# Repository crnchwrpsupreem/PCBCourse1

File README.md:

# PCBCourse1
Course 1 of 3 PCB design courses through Fedevel: Phils Lab Mixed signal hardware design with Kicad

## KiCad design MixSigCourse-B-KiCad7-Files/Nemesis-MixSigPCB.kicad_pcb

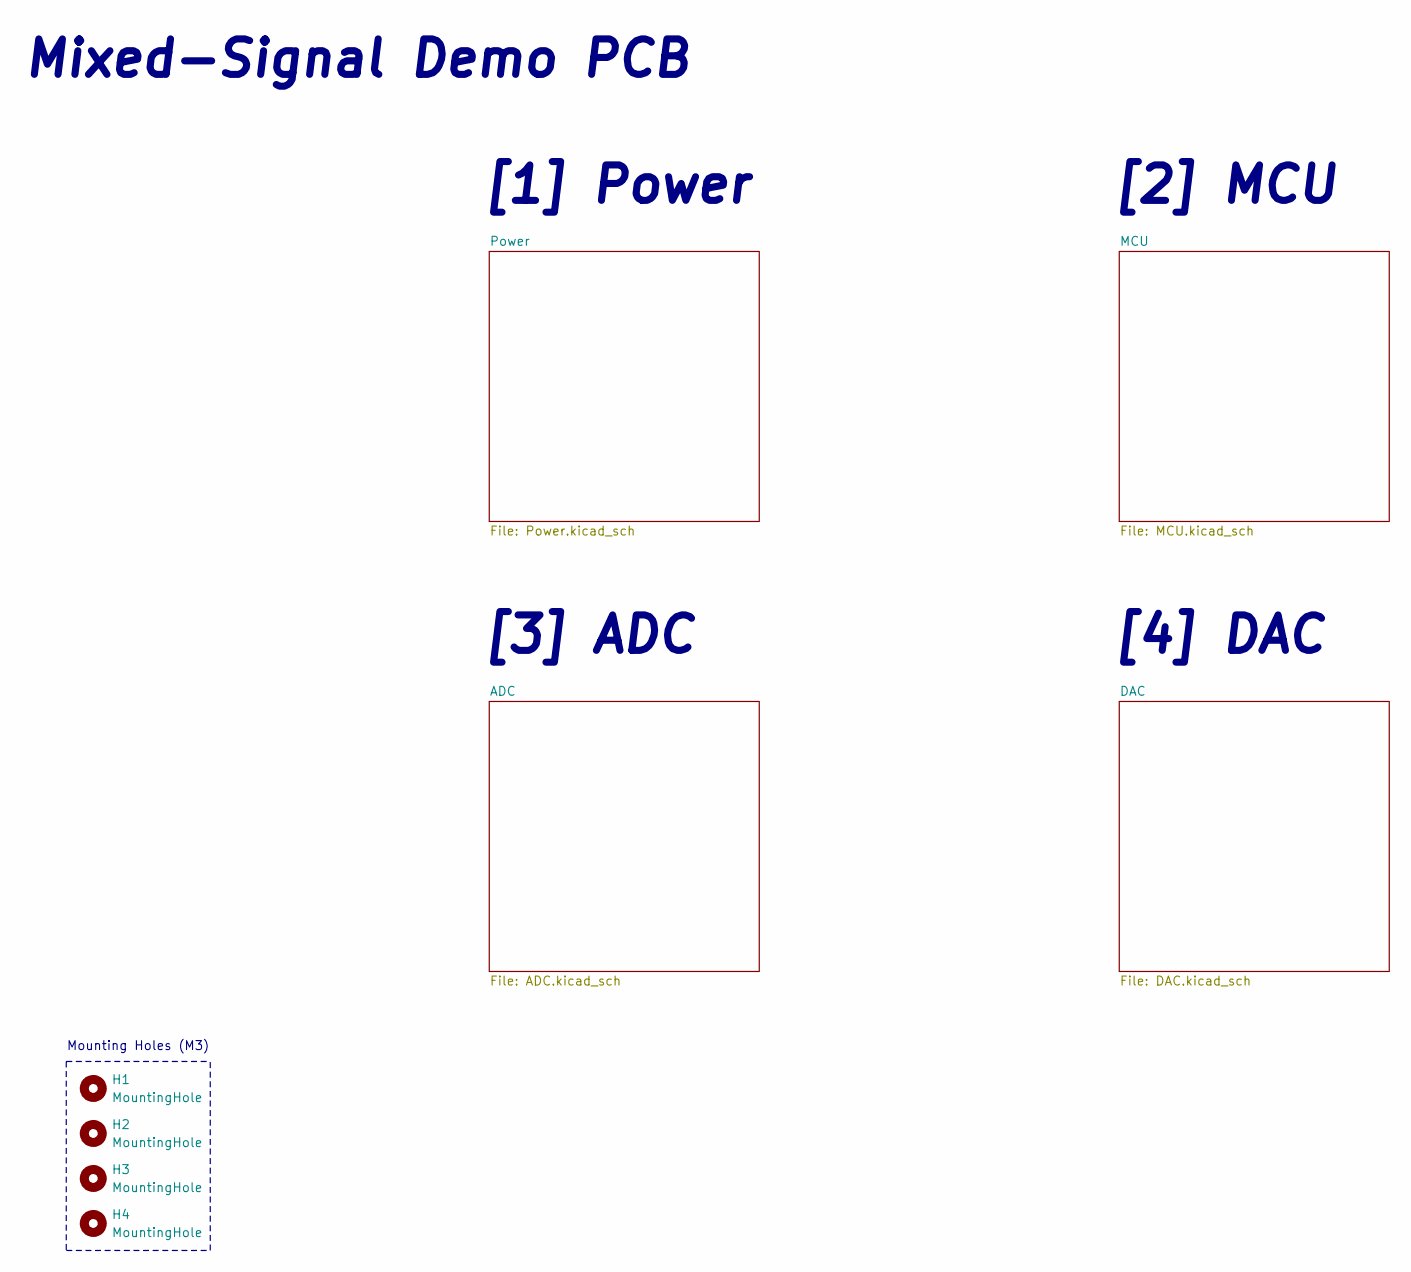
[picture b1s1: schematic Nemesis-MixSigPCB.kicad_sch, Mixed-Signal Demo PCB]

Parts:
H1, H2, H3, H4: MountingHole; MountingHole_3.2mm_M3

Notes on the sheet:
[4] DAC
Mixed-Signal Demo PCB
[3] ADC
Mounting Holes (M3)
[2] MCU
[1] Power

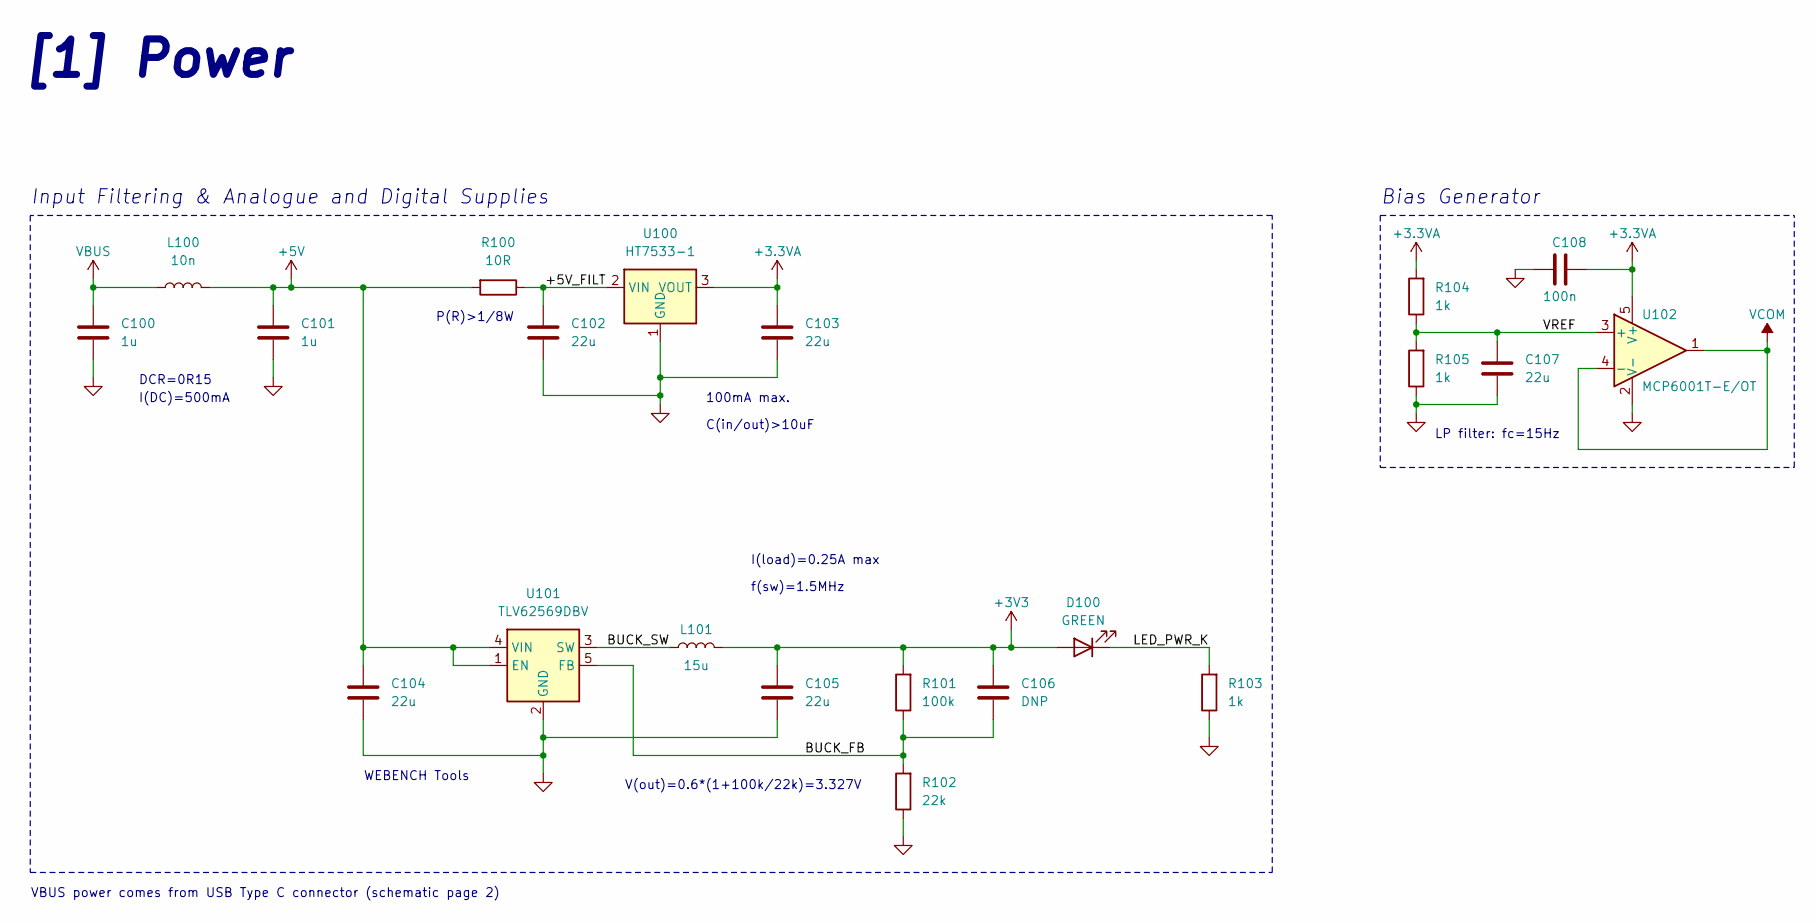
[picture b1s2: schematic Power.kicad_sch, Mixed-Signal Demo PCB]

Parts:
C100, C101: 1u; C_0603_1608Metric
C102, C103, C104, C105, C107: 22u; C_0805_2012Metric
C106: DNP; C_0402_1005Metric
C108: 100n; C_0402_1005Metric
D100: GREEN; LED_0603_1608Metric
L100: 10n; L_0402_1005Metric
L101: 15u; MWSA0603S
R100: 10R; R_0805_2012Metric
R101: 100k; R_0402_1005Metric
R102: 22k; R_0402_1005Metric
R103, R104, R105: 1k; R_0402_1005Metric
U100: HT7533-1; SOT-89-3
U101: TLV62569DBV; SOT-23-5
U102: MCP6001T-E/OT; SOT-23-5

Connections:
+3.3VA: C103.1, C108.1, R104.2, U100.3 (VOUT), U102.5 (V+); also elsewhere on the board
+3V3: C105.1, C106.1, D100.2 (A), L101.2, R101.2; also elsewhere on the board
+5V: C101.1, C104.1, L100.2, R100.2, U101.1 (EN), U101.4 (VIN); also elsewhere on the board
/Power/+5V_FILT: C102.1, R100.1, U100.2 (VIN)
/Power/BUCK_FB: C106.2, R101.1, R102.2, U101.5 (FB)
/Power/BUCK_SW: L101.1, U101.3 (SW)
/Power/LED_PWR_K: D100.1 (K), R103.2
/Power/VREF: C107.1, R104.1, R105.2, U102.3 (+)
GND: C100.2, C101.2, C102.2, C103.2, C104.2, C105.2, C107.2, C108.2, R102.1, R103.1, R105.1, U100.1 (GND), U101.2 (GND), U102.2 (V-); also elsewhere on the board
VBUS: C100.1, L100.1; also elsewhere on the board
VCOM: U102.1, U102.4 (-); also elsewhere on the board

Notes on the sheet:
DCR=0R15
C(in/out)>10uF
V(out)=0.6*(1+100k/22k)=3.327V
I(DC)=500mA
Bias Generator
LP filter: fc=15Hz
100mA max.
f(sw)=1.5MHz
VBUS power comes from USB Type C connector (schematic page 2)
P(R)>1/8W
I(load)=0.25A max
Input Filtering & Analogue and Digital Supplies
[1] Power
WEBENCH Tools

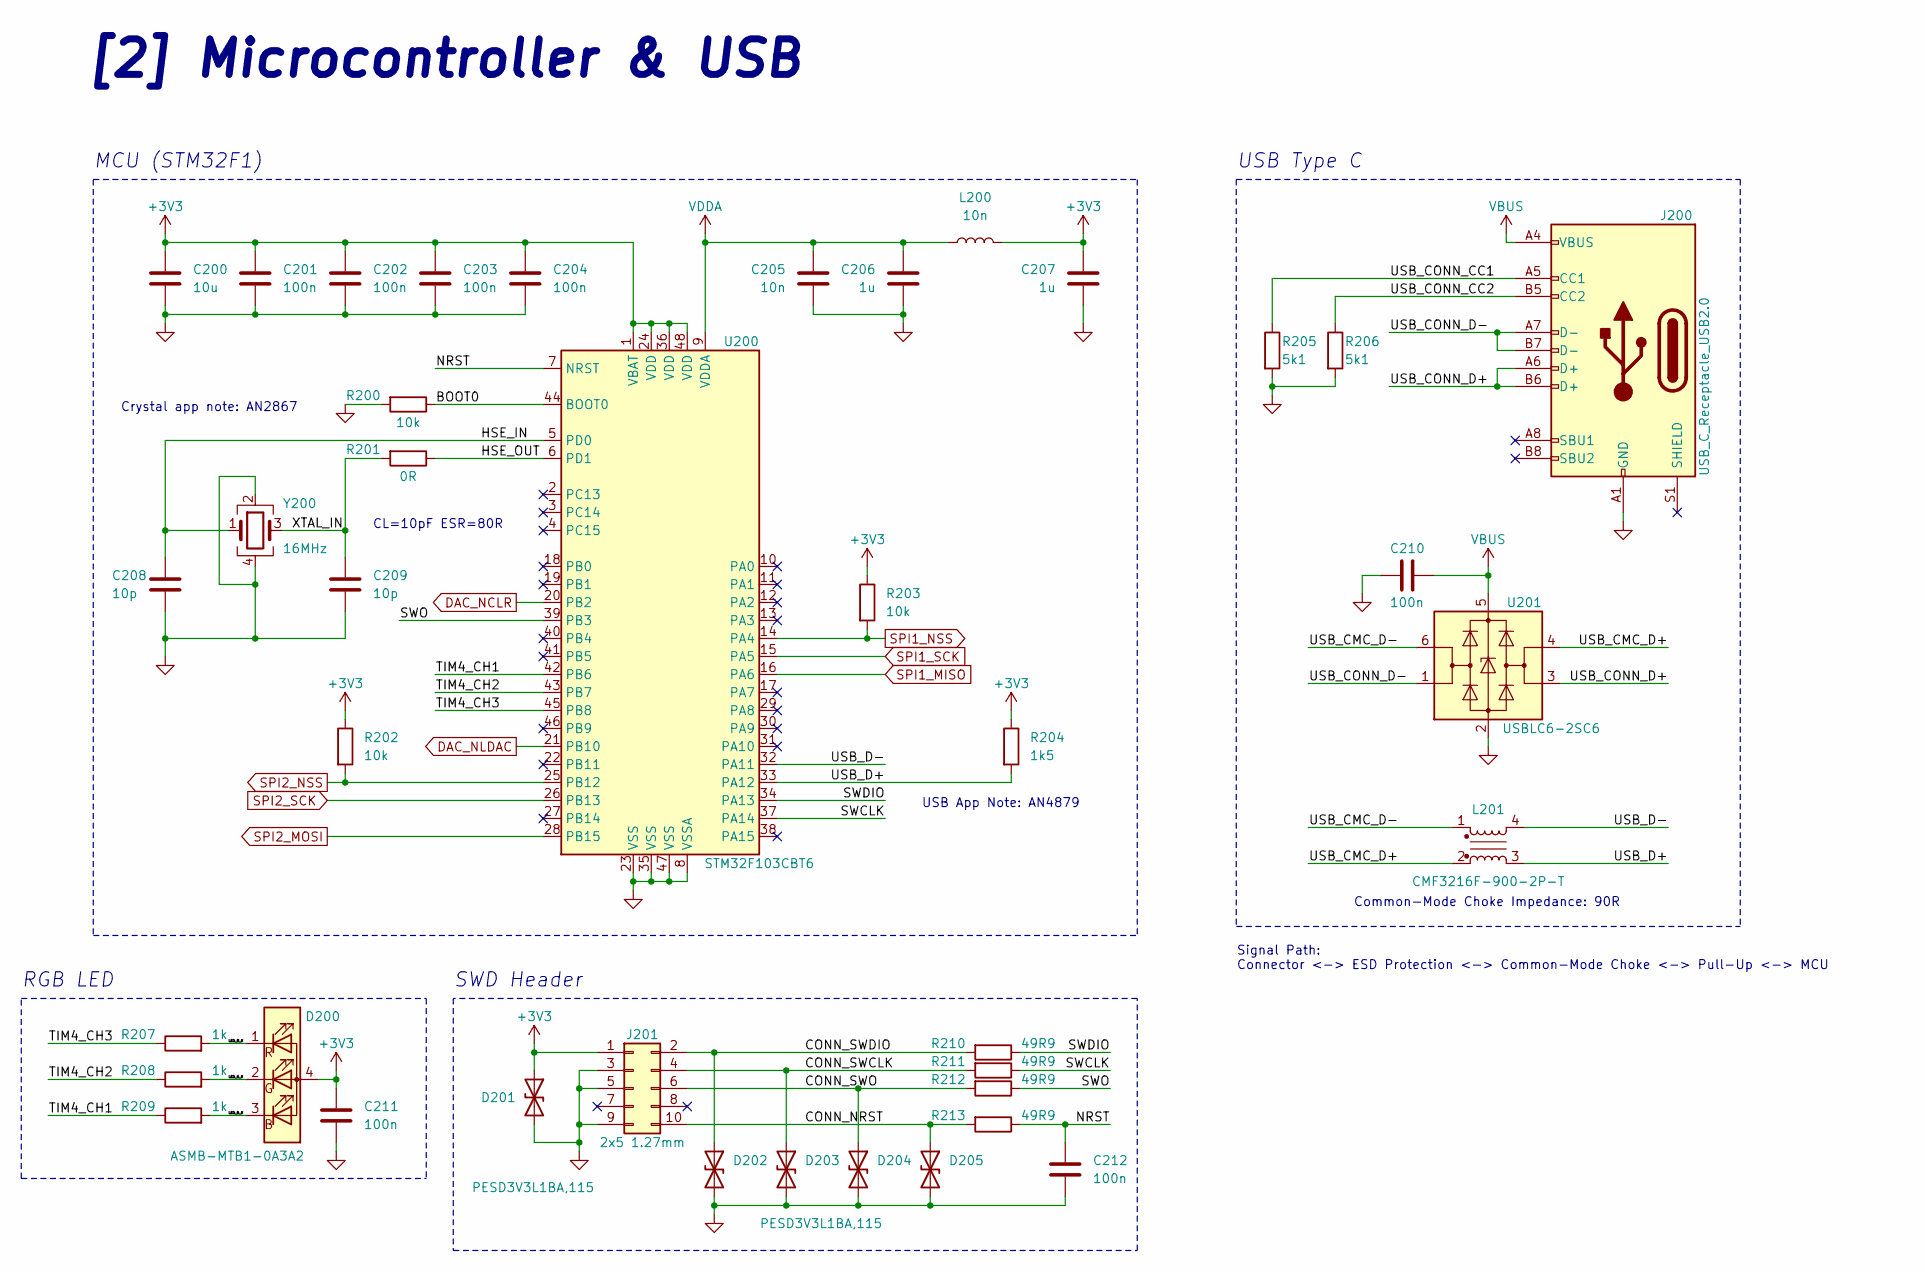
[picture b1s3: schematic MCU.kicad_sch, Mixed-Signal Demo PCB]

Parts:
C200: 10u; C_0603_1608Metric
C201, C202, C203, C204, C210, C211, C212: 100n; C_0402_1005Metric
C205: 10n; C_0402_1005Metric
C206, C207: 1u; C_0603_1608Metric
C208, C209: 10p; C_0402_1005Metric
D200: ASMB-MTB1-0A3A2; LED_Avago_PLCC4_3.2x2.8mm_CW
D201, D202, D203, D204, D205: PESD3V3L1BA,115; D_SOD-323
J200: USB_C_Receptacle_USB2.0; USB_C_Receptacle_HRO_TYPE-C-31-M-12
J201: 2x5 1.27mm; PinHeader_2x05_P1.27mm_Vertical_SMD
L200: 10n; L_0402_1005Metric
L201: CMF3216F-900-2P-T; CMC-1206
R200, R202, R203: 10k; R_0402_1005Metric
R201: 0R; R_0402_1005Metric
R204: 1k5; R_0402_1005Metric
R205, R206: 5k1; R_0402_1005Metric
R207, R208, R209: 1k; R_0402_1005Metric
R210, R211, R212, R213: 49R9; R_0402_1005Metric
U200: STM32F103CBT6; LQFP-48_7x7mm_P0.5mm; Manufacturer Part Number STM32F103CBT6
U201: USBLC6-2SC6; SOT-23-6
Y200: 16MHz; Crystal_SMD_3225-4Pin_3.2x2.5mm

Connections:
+3V3: C200.1, C201.1, C202.1, C203.1, C204.1, C207.1, C211.1, D200.4 (A), D201.1 (A1), J201.1, L200.2, R202.1, R203.1, R204.1, U200.1 (VBAT), U200.24 (VDD), U200.36 (VDD), U200.48 (VDD); also elsewhere on the board
/MCU/BOOT0: R200.1, U200.44 (BOOT0)
/MCU/CONN_NRST: D205.1 (A1), J201.10, R213.2
/MCU/CONN_SWCLK: D203.1 (A1), J201.4, R211.2
/MCU/CONN_SWDIO: D202.1 (A1), J201.2, R210.2
/MCU/CONN_SWO: D204.1 (A1), J201.6, R212.2
/MCU/HSE_IN: C208.1, U200.5 (PD0), Y200.1
/MCU/HSE_OUT: R201.1, U200.6 (PD1)
/MCU/LED_B_K: D200.3 (BK), R209.2
/MCU/LED_G_K: D200.2 (GK), R208.2
/MCU/LED_R_K: D200.1 (RK), R207.2
/MCU/NRST: C212.1, R213.1, U200.7 (NRST)
/MCU/SWCLK: R211.1, U200.37 (PA14)
/MCU/SWDIO: R210.1, U200.34 (PA13)
/MCU/SWO: R212.1, U200.39 (PB3)
/MCU/TIM4_CH1: R209.1, U200.42 (PB6)
/MCU/TIM4_CH2: R208.1, U200.43 (PB7)
/MCU/TIM4_CH3: R207.1, U200.45 (PB8)
/MCU/USB_CMC_D+: L201.2, U201.4 (I/O2)
/MCU/USB_CMC_D-: L201.1, U201.6 (I/O1)
/MCU/USB_CONN_CC1: J200.A5 (CC1), R205.1
/MCU/USB_CONN_CC2: J200.B5 (CC2), R206.1
/MCU/USB_CONN_D+: J200.A6 (D+), J200.B6 (D+), U201.3 (I/O2)
/MCU/USB_CONN_D-: J200.A7 (D-), J200.B7 (D-), U201.1 (I/O1)
/MCU/USB_D+: L201.3, R204.2, U200.33 (PA12)
/MCU/USB_D-: L201.4, U200.32 (PA11)
/MCU/XTAL_IN: C209.1, R201.2, Y200.3
DAC_NCLR: U200.20 (PB2); also elsewhere on the board
DAC_NLDAC: U200.21 (PB10); also elsewhere on the board
GND: C200.2, C201.2, C202.2, C203.2, C204.2, C205.2, C206.2, C207.2, C208.2, C209.2, C210.2, C211.2, C212.2, D201.2 (A2), D202.2 (A2), D203.2 (A2), D204.2 (A2), D205.2 (A2), J200.A1 (GND), J200.A12 (GND), J200.B1 (GND), J200.B12 (GND), J201.3, J201.5, J201.9, R200.2, R205.2, R206.2, U200.8 (VSSA), U200.23 (VSS), U200.35 (VSS), U200.47 (VSS), U201.2 (GND), Y200.2, Y200.4; also elsewhere on the board
SPI1_MISO: U200.16 (PA6); also elsewhere on the board
SPI1_NSS: R203.2, U200.14 (PA4); also elsewhere on the board
SPI1_SCK: U200.15 (PA5); also elsewhere on the board
SPI2_MOSI: U200.28 (PB15); also elsewhere on the board
SPI2_NSS: R202.2, U200.25 (PB12); also elsewhere on the board
SPI2_SCK: U200.26 (PB13); also elsewhere on the board
VBUS: C210.1, J200.A4 (VBUS), J200.A9 (VBUS), J200.B4 (VBUS), J200.B9 (VBUS), U201.5 (VBUS); also elsewhere on the board
VDDA: C205.1, C206.1, L200.1, U200.9 (VDDA)

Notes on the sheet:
Signal Path: Connector <-> ESD Protection <-> Common-Mode Choke <-> Pull-Up <-> MCU
RGB LED
Crystal app note: AN2867
SWD Header
USB App Note: AN4879
Common-Mode Choke Impedance: 90R
[2] Microcontroller & USB
CL=10pF ESR=80R
MCU (STM32F1)
USB Type C

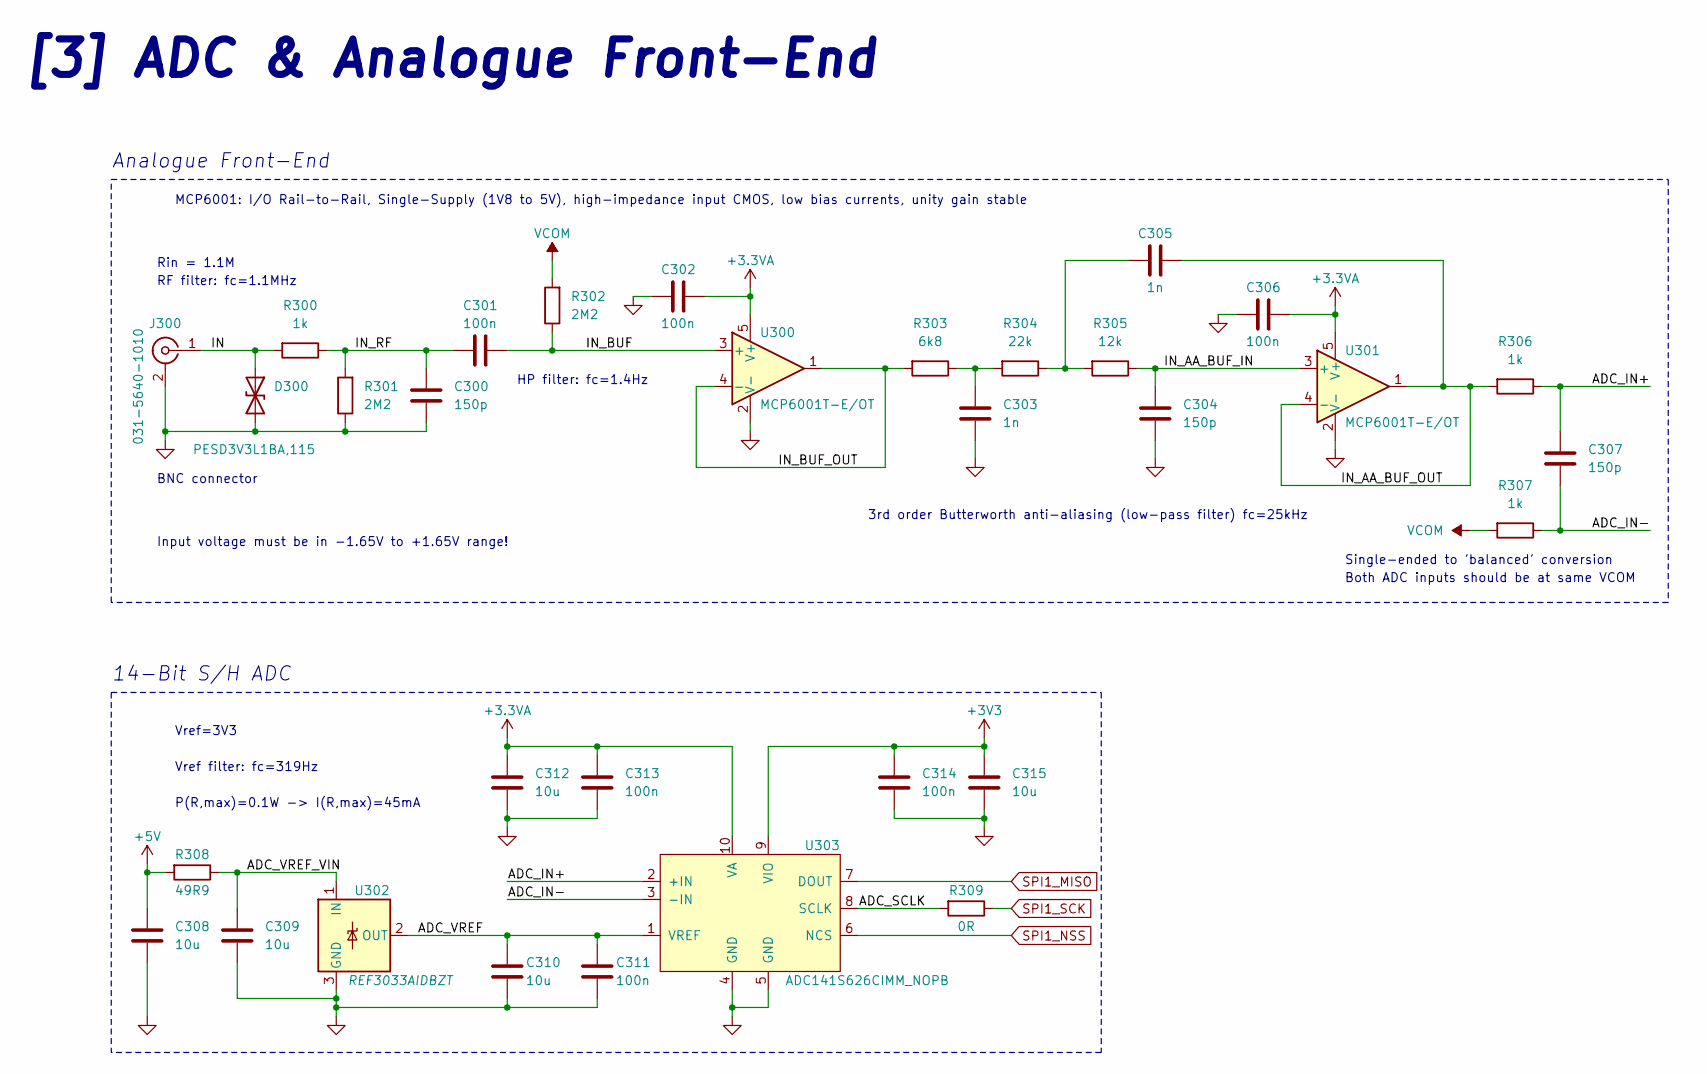
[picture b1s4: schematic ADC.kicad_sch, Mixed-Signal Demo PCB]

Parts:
C300, C304, C307: 150p; C_0402_1005Metric
C301, C302, C306, C311, C313, C314: 100n; C_0402_1005Metric
C303, C305: 1n; C_0402_1005Metric
C308, C309, C310, C312, C315: 10u; C_0603_1608Metric
D300: PESD3V3L1BA,115; D_SOD-323
J300: 031-5640-1010; AMPHENOL-BNC-031-5640-1010
R300, R306, R307: 1k; R_0402_1005Metric
R301, R302: 2M2; R_0402_1005Metric
R303: 6k8; R_0402_1005Metric
R304: 22k; R_0402_1005Metric
R305: 12k; R_0402_1005Metric
R308: 49R9; R_0402_1005Metric
R309: 0R; R_0402_1005Metric
U300, U301: MCP6001T-E/OT; SOT-23-5
U302: REF3033AIDBZT; SOT-23
U303: ADC141S626CIMM_NOPB; VSSOP-10

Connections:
+3.3VA: C302.1, C306.1, C312.1, C313.1, U300.5 (V+), U301.5 (V+), U303.10 (VA); also elsewhere on the board
+3V3: C314.1, C315.1, U303.9 (VIO); also elsewhere on the board
+5V: C308.1, R308.2; also elsewhere on the board
/ADC/ADC_IN+: C307.1, R306.1, U303.2 (+IN)
/ADC/ADC_IN-: C307.2, R307.1, U303.3 (-IN)
/ADC/ADC_SCLK: R309.2, U303.8 (SCLK)
/ADC/ADC_VREF: C310.1, C311.1, U302.2 (OUT), U303.1 (VREF)
/ADC/ADC_VREF_VIN: C309.1, R308.1, U302.1 (IN)
/ADC/IN: D300.1 (A1), J300.1 (In), R300.2
/ADC/IN_AA_BUF_IN: C304.1, R305.1, U301.3 (+)
/ADC/IN_AA_BUF_OUT: C305.2, R306.2, U301.1, U301.4 (-)
/ADC/IN_BUF: C301.1, R302.1, U300.3 (+)
/ADC/IN_BUF_OUT: R303.2, U300.1, U300.4 (-)
/ADC/IN_RF: C300.1, C301.2, R300.1, R301.2
GND: C300.2, C302.2, C303.2, C304.2, C306.2, C308.2, C309.2, C310.2, C311.2, C312.2, C313.2, C314.2, C315.2, D300.2 (A2), J300.2 (Ext), R301.1, U300.2 (V-), U301.2 (V-), U302.3 (GND), U303.4 (GND), U303.5 (GND); also elsewhere on the board
unnamed: C303.1, R303.1, R304.2
unnamed: C305.1, R304.1, R305.2
SPI1_MISO: U303.7 (DOUT); also elsewhere on the board
SPI1_NSS: U303.6 (NCS); also elsewhere on the board
SPI1_SCK: R309.1; also elsewhere on the board
VCOM: R302.2, R307.2; also elsewhere on the board

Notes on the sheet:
HP filter: fc=1.4Hz
Both ADC inputs should be at same VCOM
BNC connector
Rin = 1.1M
14-Bit S/H ADC
Vref filter: fc=319Hz
Input voltage must be in -1.65V to +1.65V range!
Analogue Front-End
Single-ended to 'balanced' conversion
RF filter: fc=1.1MHz
3rd order Butterworth anti-aliasing (low-pass filter) fc=25kHz
MCP6001: I/O Rail-to-Rail, Single-Supply (1V8 to 5V), high-impedance input CMOS, low bias currents, unity gain stable
P(R,max)=0.1W -> I(R,max)=45mA
Vref=3V3
[3] ADC & Analogue Front-End

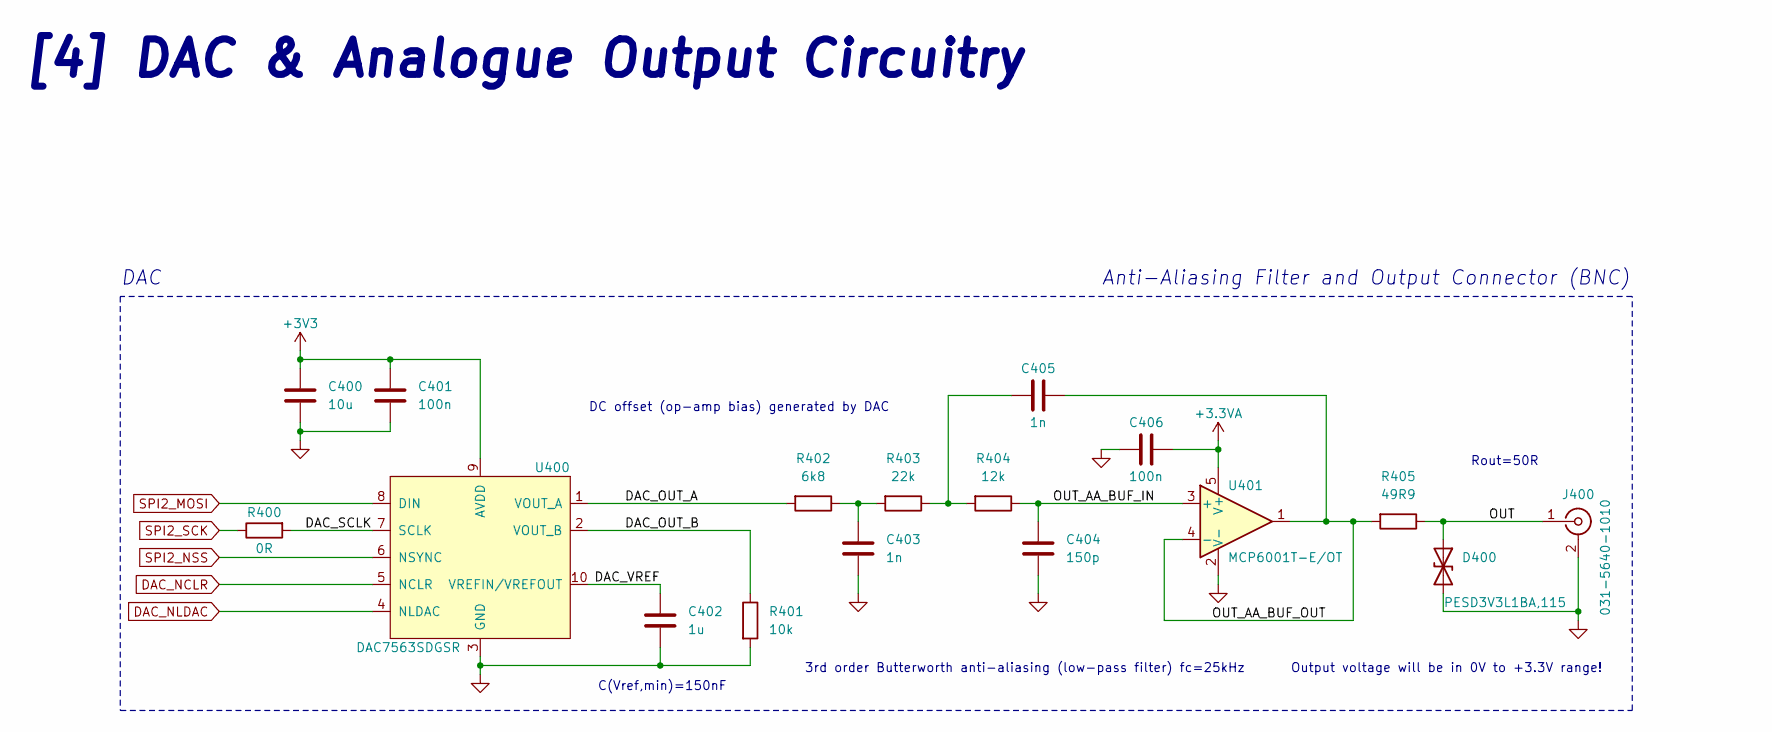
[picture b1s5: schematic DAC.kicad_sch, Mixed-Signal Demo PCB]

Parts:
C400: 10u; C_0603_1608Metric
C401, C406: 100n; C_0402_1005Metric
C402: 1u; C_0603_1608Metric
C403, C405: 1n; C_0402_1005Metric
C404: 150p; C_0402_1005Metric
D400: PESD3V3L1BA,115; D_SOD-323
J400: 031-5640-1010; AMPHENOL-BNC-031-5640-1010
R400: 0R; R_0402_1005Metric
R401: 10k; R_0402_1005Metric
R402: 6k8; R_0402_1005Metric
R403: 22k; R_0402_1005Metric
R404: 12k; R_0402_1005Metric
R405: 49R9; R_0402_1005Metric
U400: DAC7563SDGSR; VSSOP-10
U401: MCP6001T-E/OT; SOT-23-5

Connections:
+3.3VA: C406.1, U401.5 (V+); also elsewhere on the board
+3V3: C400.1, C401.1, U400.9 (AVDD); also elsewhere on the board
/DAC/DAC_OUT_A: R402.2, U400.1 (VOUT_A)
/DAC/DAC_OUT_B: R401.1, U400.2 (VOUT_B)
/DAC/DAC_SCLK: R400.2, U400.7 (SCLK)
/DAC/DAC_VREF: C402.1, U400.10 (VREFIN/VREFOUT)
/DAC/OUT: D400.1 (A1), J400.1 (In), R405.1
/DAC/OUT_AA_BUF_IN: C404.1, R404.1, U401.3 (+)
/DAC/OUT_AA_BUF_OUT: C405.2, R405.2, U401.1, U401.4 (-)
DAC_NCLR: U400.5 (NCLR); also elsewhere on the board
DAC_NLDAC: U400.4 (NLDAC); also elsewhere on the board
GND: C400.2, C401.2, C402.2, C403.2, C404.2, C406.2, D400.2 (A2), J400.2 (Ext), R401.2, U400.3 (GND), U401.2 (V-); also elsewhere on the board
unnamed: C403.1, R402.1, R403.2
unnamed: C405.1, R403.1, R404.2
SPI2_MOSI: U400.8 (DIN); also elsewhere on the board
SPI2_NSS: U400.6 (NSYNC); also elsewhere on the board
SPI2_SCK: R400.1; also elsewhere on the board

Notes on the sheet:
[4] DAC & Analogue Output Circuitry
Anti-Aliasing Filter and Output Connector (BNC)
Rout=50R
Output voltage will be in 0V to +3.3V range!
DAC
C(Vref,min)=150nF
3rd order Butterworth anti-aliasing (low-pass filter) fc=25kHz
DC offset (op-amp bias) generated by DAC

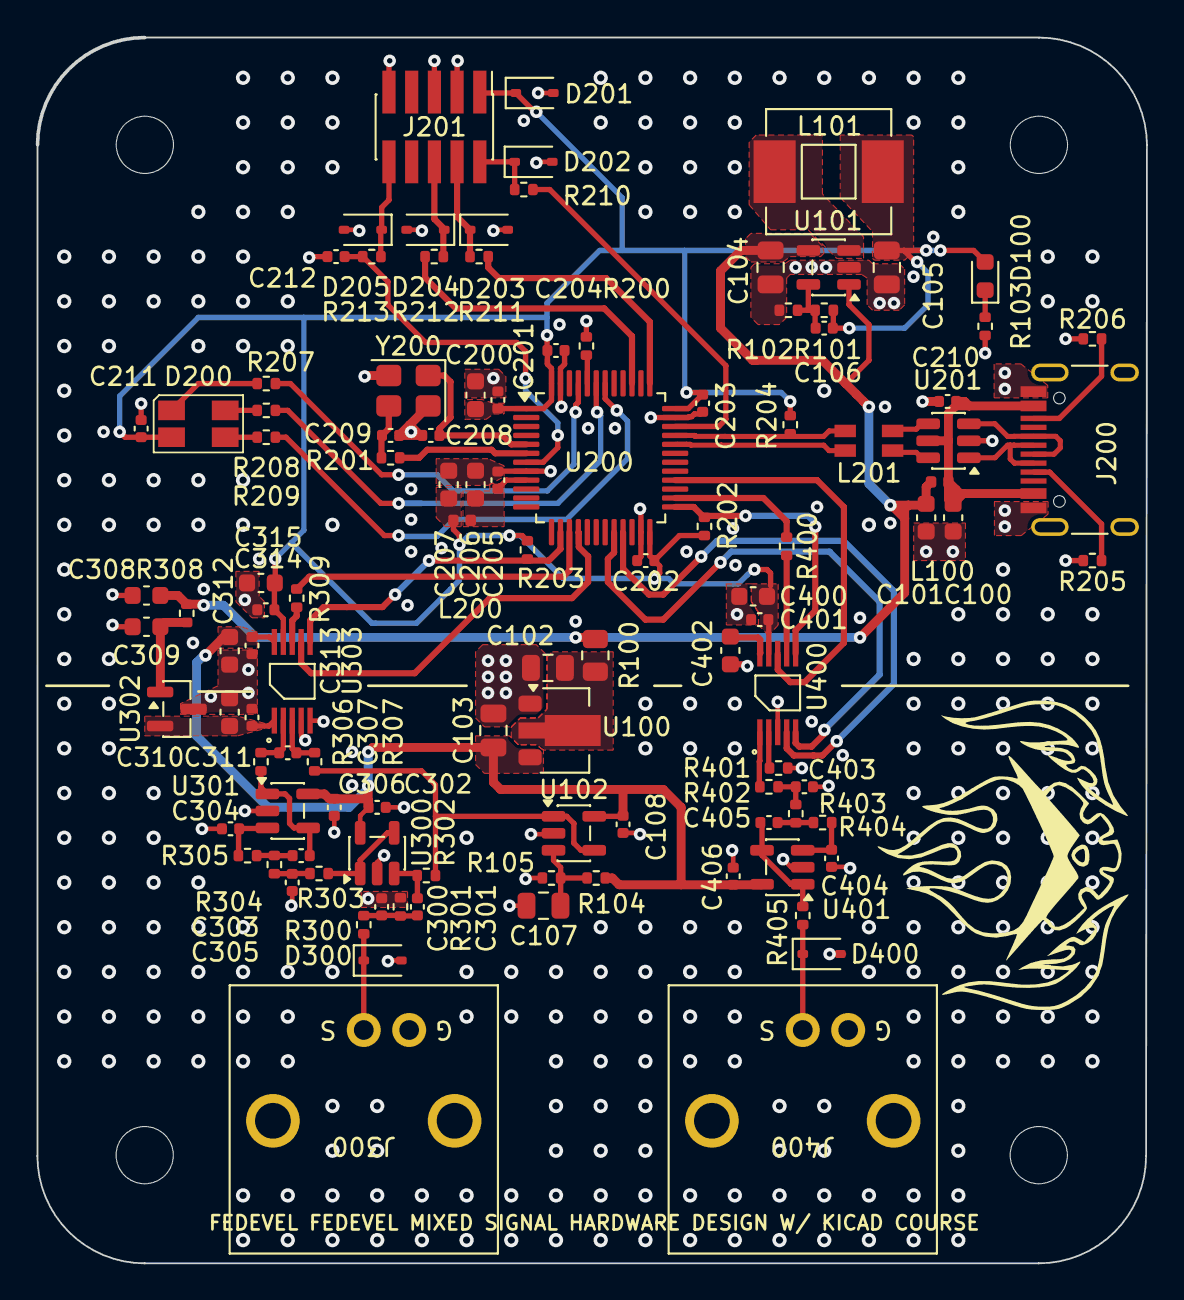
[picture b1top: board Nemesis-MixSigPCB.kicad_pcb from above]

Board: 4 copper layers, 62.0 x 68.5 mm, 114 parts (0 on the bottom side), 68 nets.

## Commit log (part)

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2025-09-17 added the default project provided with the Fedevel Course
    generally will not be modifying this, will add a different folder for other modded versions
2025-11-04 completed the course! board layout complete and gerbers exported
